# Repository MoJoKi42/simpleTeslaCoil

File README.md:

# simpleTeslaCoil
just a simple TeslaCoil (SSTC) with basic components

<ins>Few facts:</ins>
- 12-24V input voltage
- around 3-4A current maximum
- up to 550kHz frequency possible
- 100x100mm board

Picture of the finished board:

And a picture of my final construction with coil and PSU:

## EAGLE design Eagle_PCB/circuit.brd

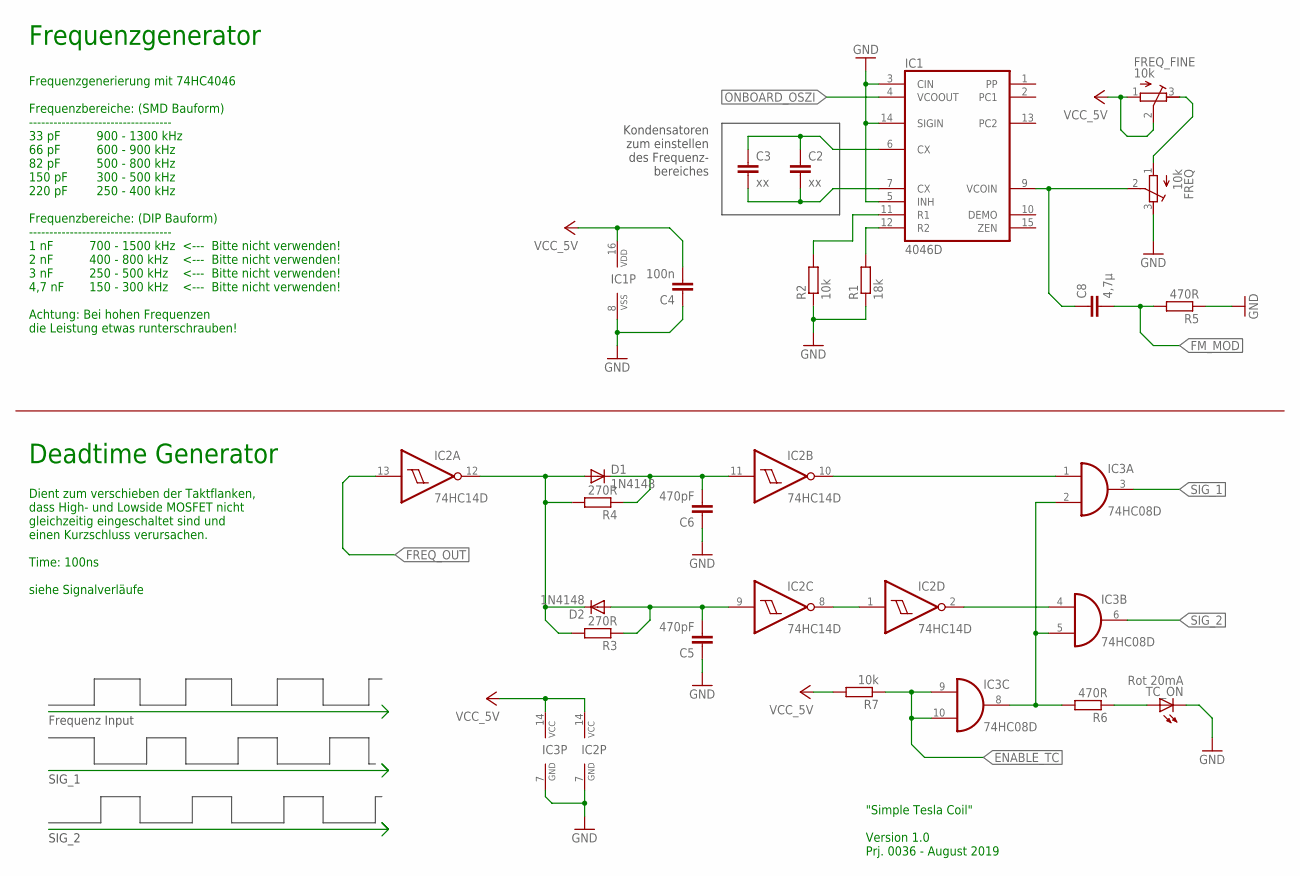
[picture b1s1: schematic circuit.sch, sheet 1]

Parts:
C2, C3: xx; C0805K
C4: 100n; C1206K
C5, C6: 470pF; C1206K
C8: 4,7µ; C1206K
D1, D2: 1N4148; SOD323-W
FREQ: 10k; RTRIM64W
FREQ_FINE: 10k; RTRIM64W
IC1: 4046D; SO16
IC2: 74HC14D; SO14
IC3: 74HC08D; SO14
R1: 18k; M1206
R2, R7: 10k; M1206
R3, R4: 270R; M1206
R5, R6: 470R; M1206
TC_ON: Rot 20mA; 1206

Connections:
ENABLE_TC: IC3.9 (I0), IC3.10 (I1), R7.1; also elsewhere on the board
ENABLE_TC2: IC3.2 (I1), IC3.5 (I1), IC3.8 (O), R6.2
FM_MOD: C8.2, R5.2; also elsewhere on the board
FREQ_OUT: IC2.13 (I); also elsewhere on the board
GND: C4.1, C5.1, C6.1, FREQ.3 (E), IC1.3 (CIN), IC1.5 (INH), IC1.8 (VSS), IC1.14 (SIGIN), IC2.7 (GND), IC3.7 (GND), R1.1, R2.1, R5.1, TC_ON.C; also elsewhere on the board
unnamed: C2.1, C3.1, IC1.6 (CX)
unnamed: C2.2, C3.2, IC1.7 (CX)
unnamed: C5.2, D2.A, IC2.9 (I), R3.1
unnamed: C8.1, FREQ.2 (S), IC1.9 (VCOIN)
unnamed: R6.1, TC_ON.A
unnamed: IC1.11 (R1), R2.2
unnamed: IC1.12 (R2), R1.2
unnamed: D1.A, D2.C, IC2.12 (O), R3.2, R4.2
unnamed: C6.2, D1.C, IC2.11 (I), R4.1
unnamed: IC2.1 (I), IC2.8 (O)
unnamed: IC2.2 (O), IC3.4 (I0)
unnamed: IC2.10 (O), IC3.1 (I0)
unnamed: FREQ.1 (A), FREQ_FINE.3 (E)
ONBOARD_OSZI: IC1.4 (VCOOUT); also elsewhere on the board
SIG_1: IC3.3 (O); also elsewhere on the board
SIG_2: IC3.6 (O); also elsewhere on the board
VCC: C4.2, FREQ_FINE.1 (A), FREQ_FINE.2 (S), IC1.16 (VDD), IC2.14 (VCC), IC3.14 (VCC), R7.2; also elsewhere on the board

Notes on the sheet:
Frequenzgenerator
Deadtime Generator
Kondensatoren zum einstellen des Frequenz- bereiches
Frequenz Input
SIG_1
SIG_2
Dient zum verschieben der Taktflanken, dass High- und Lowside MOSFET nicht gleichzeitig eingeschaltet sind und einen Kurzschluss verursachen. Time: 100ns siehe Signalverläufe
Frequenzgenerierung mit 74HC4046 Frequenzbereiche: (SMD Bauform) ----------------------------------- 33 pF 900 - 1300 kHz 66 pF 600 - 900 kHz 82 pF 500 - 800 kHz 150 pF 300 - 500 kHz 220 pF 250 - 400 kHz Frequenzbereiche: (DIP Bauform) ----------------------------------- 1 nF 700 - 1500 kHz <--- Bi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
"Simple Tesla Coil" Version 1.0 Prj. 0036 - August 2019

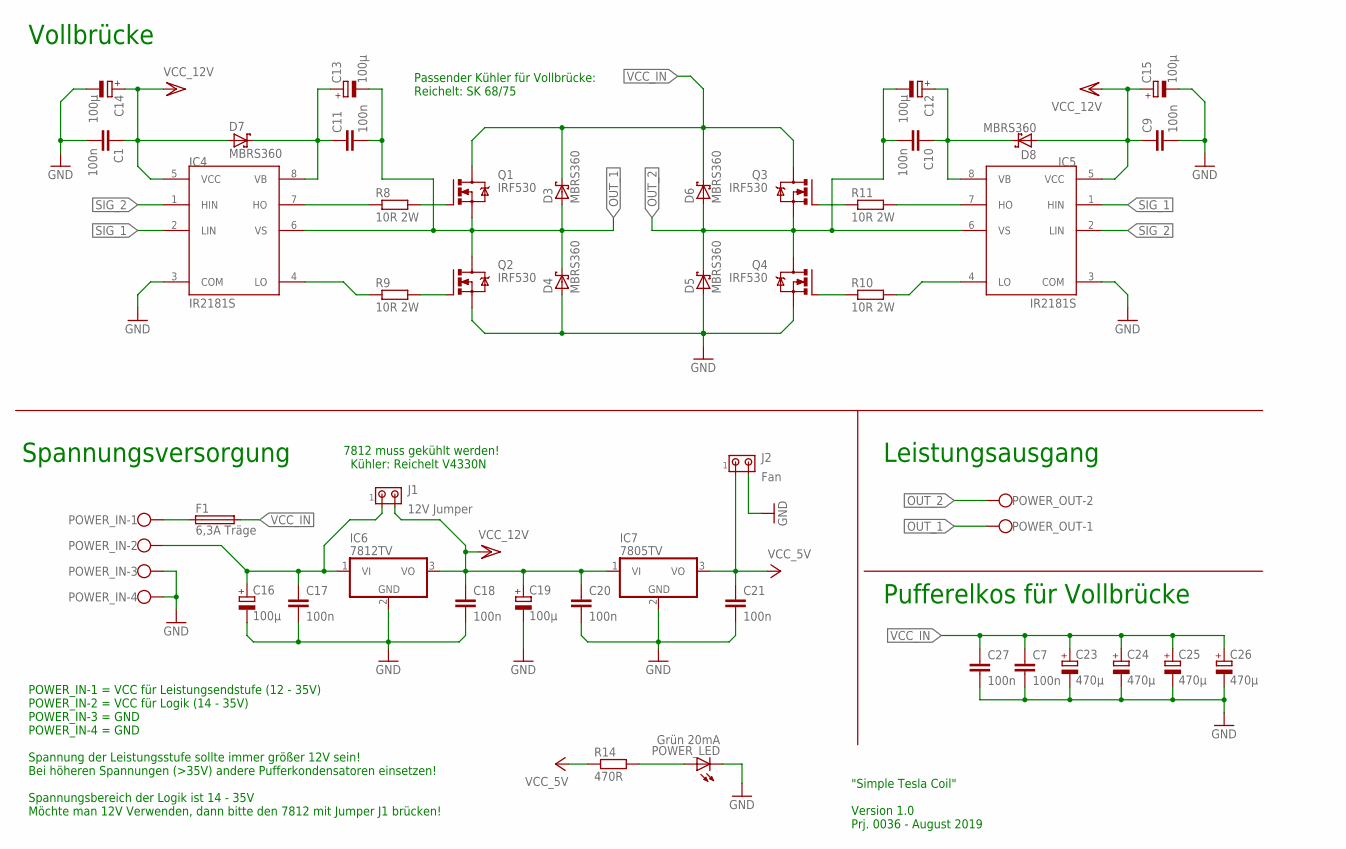
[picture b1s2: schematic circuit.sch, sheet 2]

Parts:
C1, C7, C9, C10, C11, C17, C18, C20, C21, C27: 100n; C1206K
C12, C13, C14, C15, C16, C19: 100µ; E2,5-7
C23, C24, C25, C26: 470µ; E5-10,5
D3, D4, D5, D6, D7, D8: MBRS360; SMC
F1: 6,3A Träge; SH22,5
IC4, IC5: IR2181S; SO08
IC6: 7812TV; TO220V
IC7: 7805TV; TO220V
J1: 12V Jumper; 10X02MTA
J2: Fan; 10X02MTA
POWER_IN: W237-4
POWER_LED: Grün 20mA; 1206
POWER_OUT: W237-102
Q1, Q2, Q3, Q4: IRF530; TO220BV
R8, R9, R10, R11: 10R 2W; 0411/15
R14: 470R; M1206

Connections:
GND: C1.2, C7.2, C9.2, C14.-, C15.-, C16.-, C17.2, C18.2, C19.-, C20.2, C21.2, C23.-, C24.-, C25.-, C26.-, C27.2, D4.A, D5.A, IC4.3 (COM), IC5.3 (COM), IC6.2 (GND), IC7.2 (GND), J2.2, POWER_IN.3, POWER_IN.4, POWER_LED.C, Q2.S, Q4.S; also elsewhere on the board
unnamed: IC4.7 (HO), R8.1
unnamed: IC4.4 (LO), R9.1
unnamed: IC5.7 (HO), R11.2
unnamed: IC5.4 (LO), R10.2
unnamed: F1.1, POWER_IN.1
unnamed: Q3.G, R11.1
unnamed: Q4.G, R10.1
unnamed: Q2.G, R9.2
unnamed: C16.+, C17.1, IC6.1 (VI), J1.1, POWER_IN.2
unnamed: POWER_LED.A, R14.2
unnamed: Q1.G, R8.2
OUT_1: C11.2, C13.-, D3.A, D4.C, IC4.6 (VS), POWER_OUT.1, Q1.S, Q2.D
OUT_2: C10.2, C12.-, D5.C, D6.A, IC5.6 (VS), POWER_OUT.2, Q3.S, Q4.D
SIG_1: IC4.2 (LIN), IC5.1 (HIN); also elsewhere on the board
SIG_2: IC4.1 (HIN), IC5.2 (LIN); also elsewhere on the board
VB: C11.1, C13.+, D7.C, IC4.8 (VB)
VB_2: C10.1, C12.+, D8.C, IC5.8 (VB)
VCC: C21.1, IC7.3 (VO), J2.1, R14.1; also elsewhere on the board
VCC/2: C1.1, C9.1, C14.+, C15.+, C18.1, C19.+, C20.1, D7.A, D8.A, IC4.5 (VCC), IC5.5 (VCC), IC6.3 (VO), IC7.1 (VI), J1.2; also elsewhere on the board
VCC_IN: C7.1, C23.+, C24.+, C25.+, C26.+, C27.1, D3.C, D6.C, F1.2, Q1.D, Q3.D

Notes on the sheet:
Vollbrücke
Passender Kühler für Vollbrücke: Reichelt: SK 68/75
POWER_IN-1 = VCC für Leistungsendstufe (12 - 35V) POWER_IN-2 = VCC für Logik (14 - 35V) POWER_IN-3 = GND POWER_IN-4 = GND Spannung der Leistungsstufe sollte immer größer 12V sein! Bei höheren Spannungen (>35V) andere Pufferkondensatoren einsetzen! Spannungsbereich der Logik ist 14 - 35V Möchte man 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
7812 muss gekühlt werden! Kühler: Reichelt V4330N
Spannungsversorgung
Leistungsausgang
Pufferelkos für Vollbrücke
"Simple Tesla Coil" Version 1.0 Prj. 0036 - August 2019

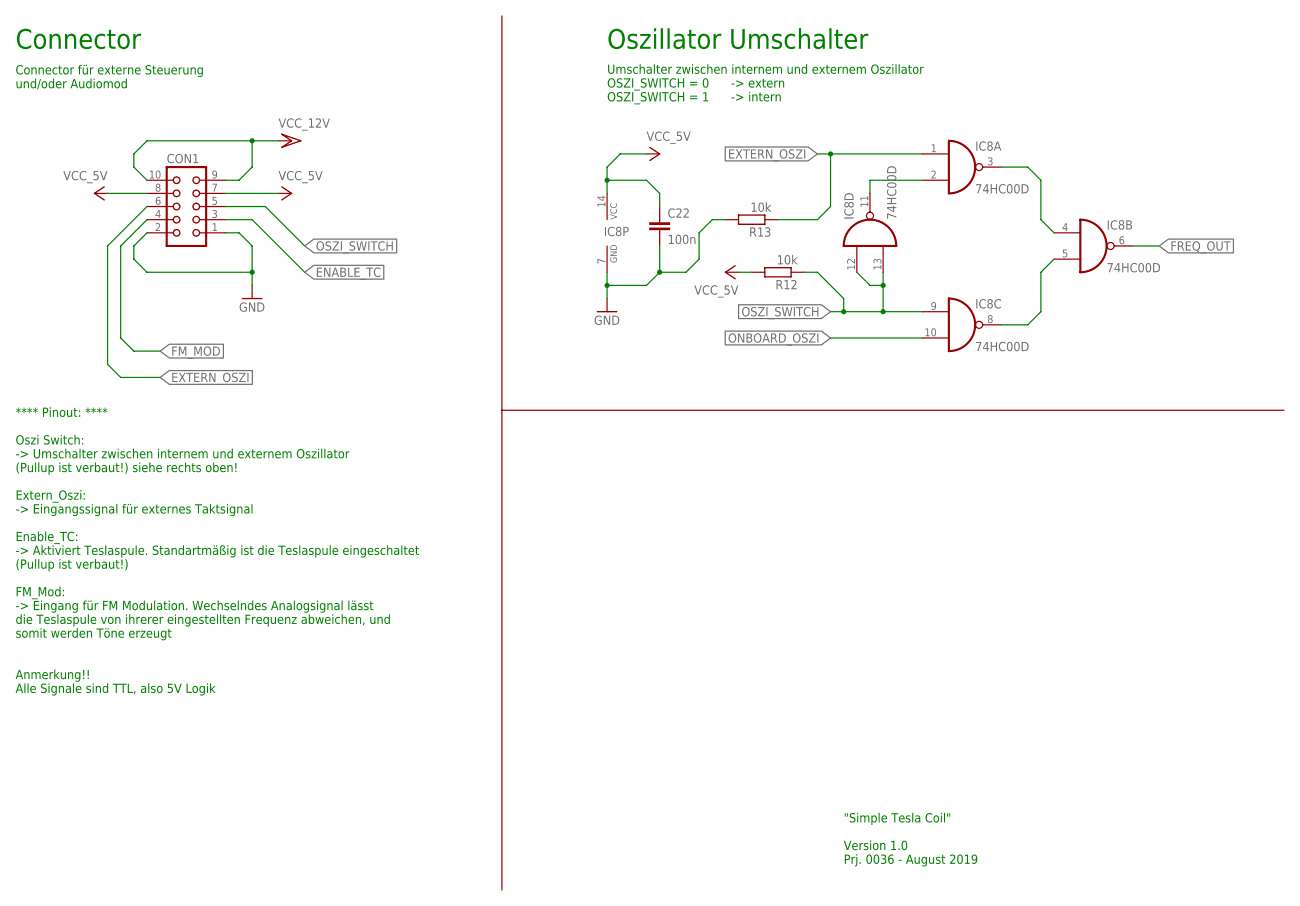
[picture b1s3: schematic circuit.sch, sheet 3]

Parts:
C22: 100n; C1206K
CON1: CON10
IC8: 74HC00D; SO14
R12, R13: 10k; M1206

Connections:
ENABLE_TC: CON1.3; also elsewhere on the board
EXTERN_OSZI: CON1.6, IC8.1 (I0), R13.1
FM_MOD: CON1.4; also elsewhere on the board
FREQ_OUT: IC8.6 (O); also elsewhere on the board
GND: C22.2, CON1.1, CON1.2, IC8.7 (GND), R13.2; also elsewhere on the board
unnamed: IC8.2 (I1), IC8.11 (O)
unnamed: IC8.3 (O), IC8.4 (I0)
unnamed: IC8.5 (I1), IC8.8 (O)
ONBOARD_OSZI: IC8.10 (I1); also elsewhere on the board
OSZI_SWITCH: CON1.5, IC8.9 (I0), IC8.12 (I0), IC8.13 (I1), R12.1
VCC: C22.1, CON1.7, CON1.8, IC8.14 (VCC), R12.2; also elsewhere on the board
VCC/2: CON1.9, CON1.10; also elsewhere on the board

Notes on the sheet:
Connector
Connector für externe Steuerung und/oder Audiomod
Oszillator Umschalter
Umschalter zwischen internem und externem Oszillator OSZI_SWITCH = 0 -> extern OSZI_SWITCH = 1 -> intern
**** Pinout: **** Oszi Switch: -> Umschalter zwischen internem und externem Oszillator (Pullup ist verbaut!) siehe rechts oben! Extern_Oszi: -> Eingangssignal für externes Taktsignal Enable_TC: -> Aktiviert Teslaspule. Standartmäßig ist die Teslaspule eingeschaltet (Pullup ist verbaut!) FM_Mod: -> 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
"Simple Tesla Coil" Version 1.0 Prj. 0036 - August 2019

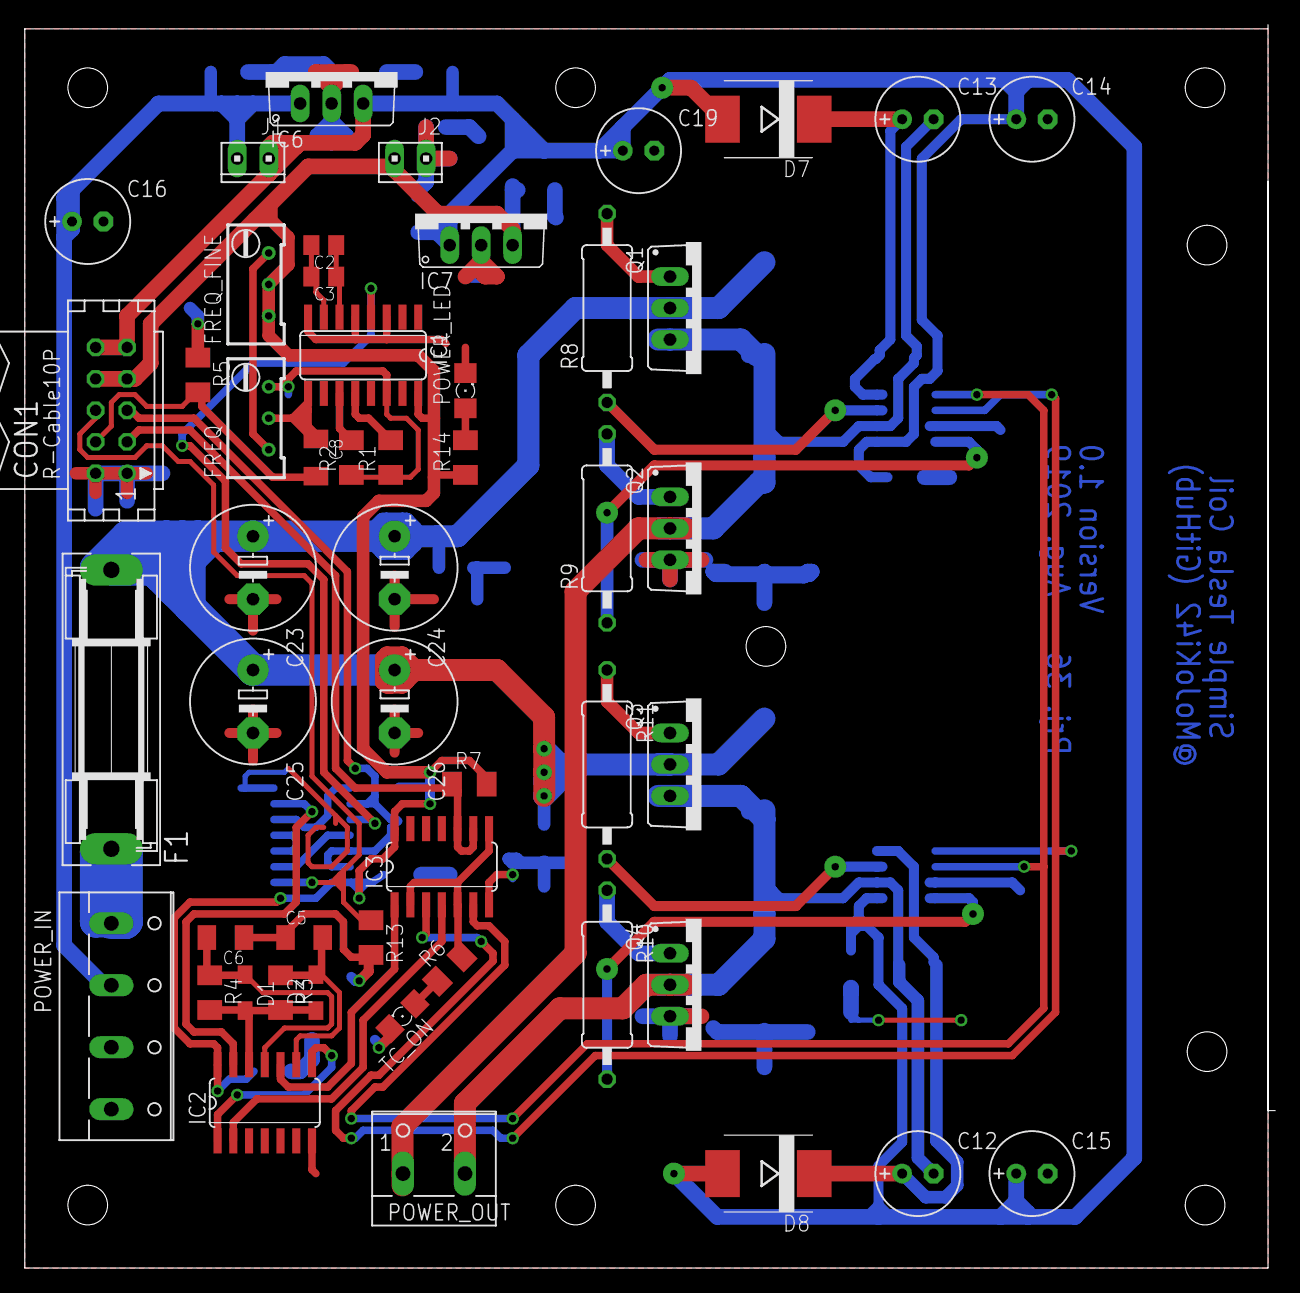
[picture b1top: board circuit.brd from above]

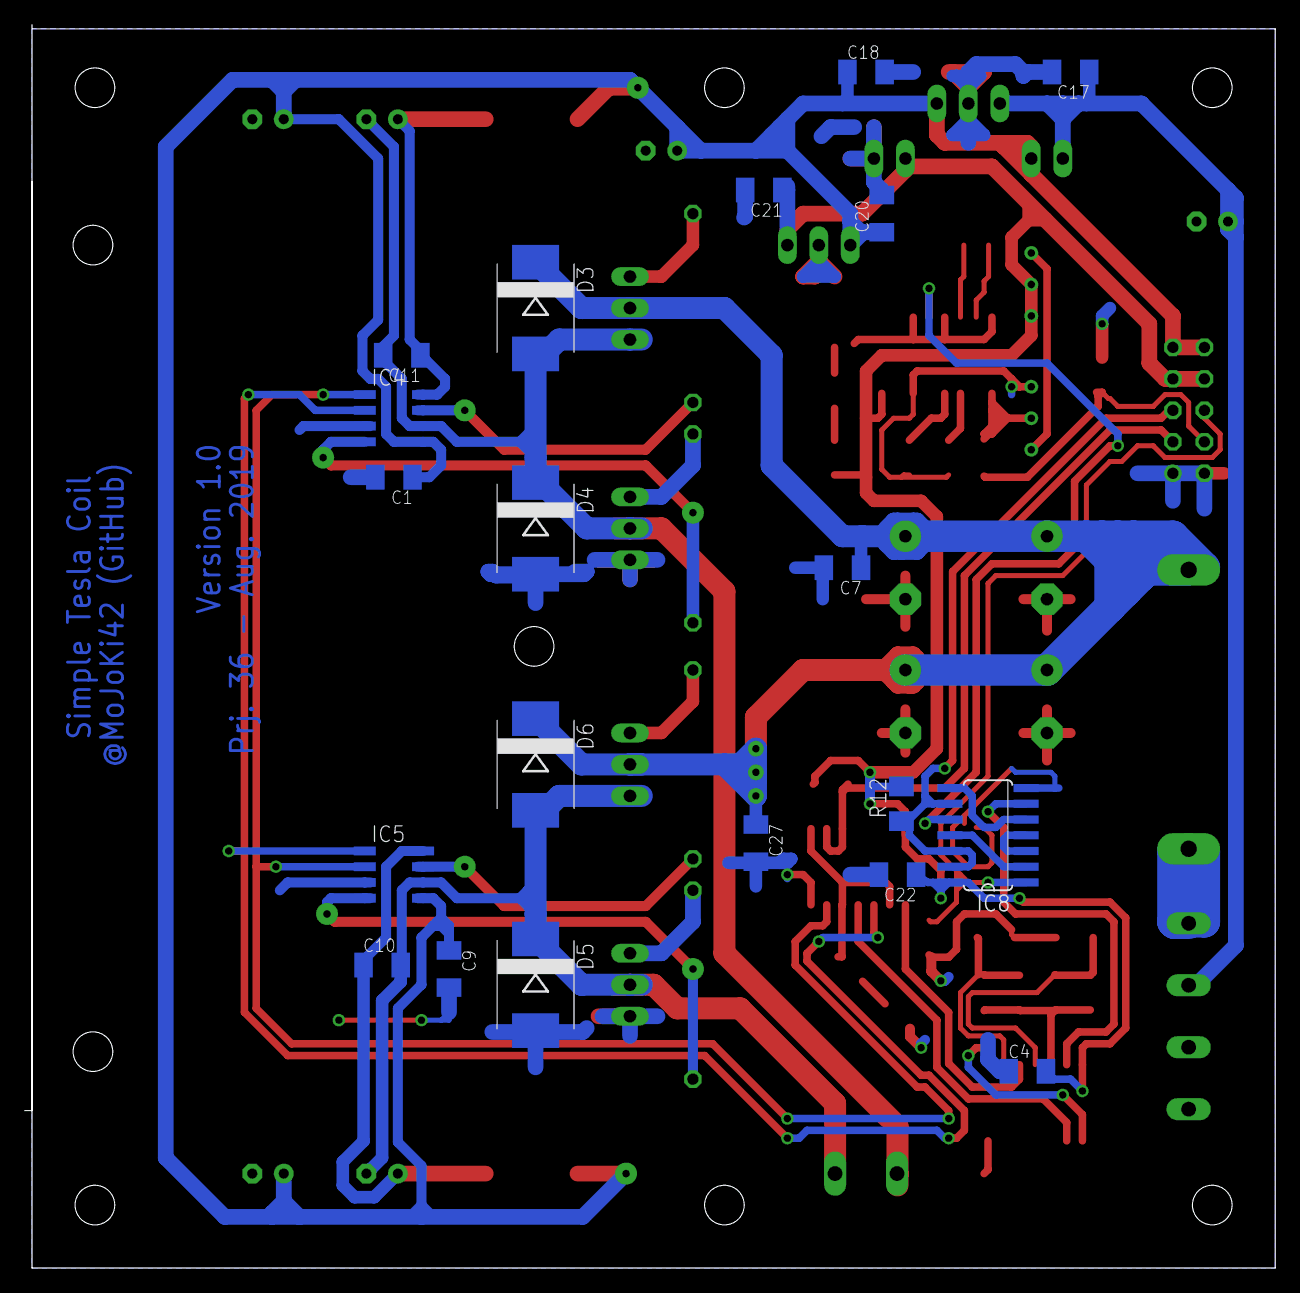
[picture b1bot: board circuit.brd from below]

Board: 2 copper layers, 100.9 x 100.3 mm, 71 parts (20 on the bottom side), 44 nets.

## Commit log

2023-03-30 inital
